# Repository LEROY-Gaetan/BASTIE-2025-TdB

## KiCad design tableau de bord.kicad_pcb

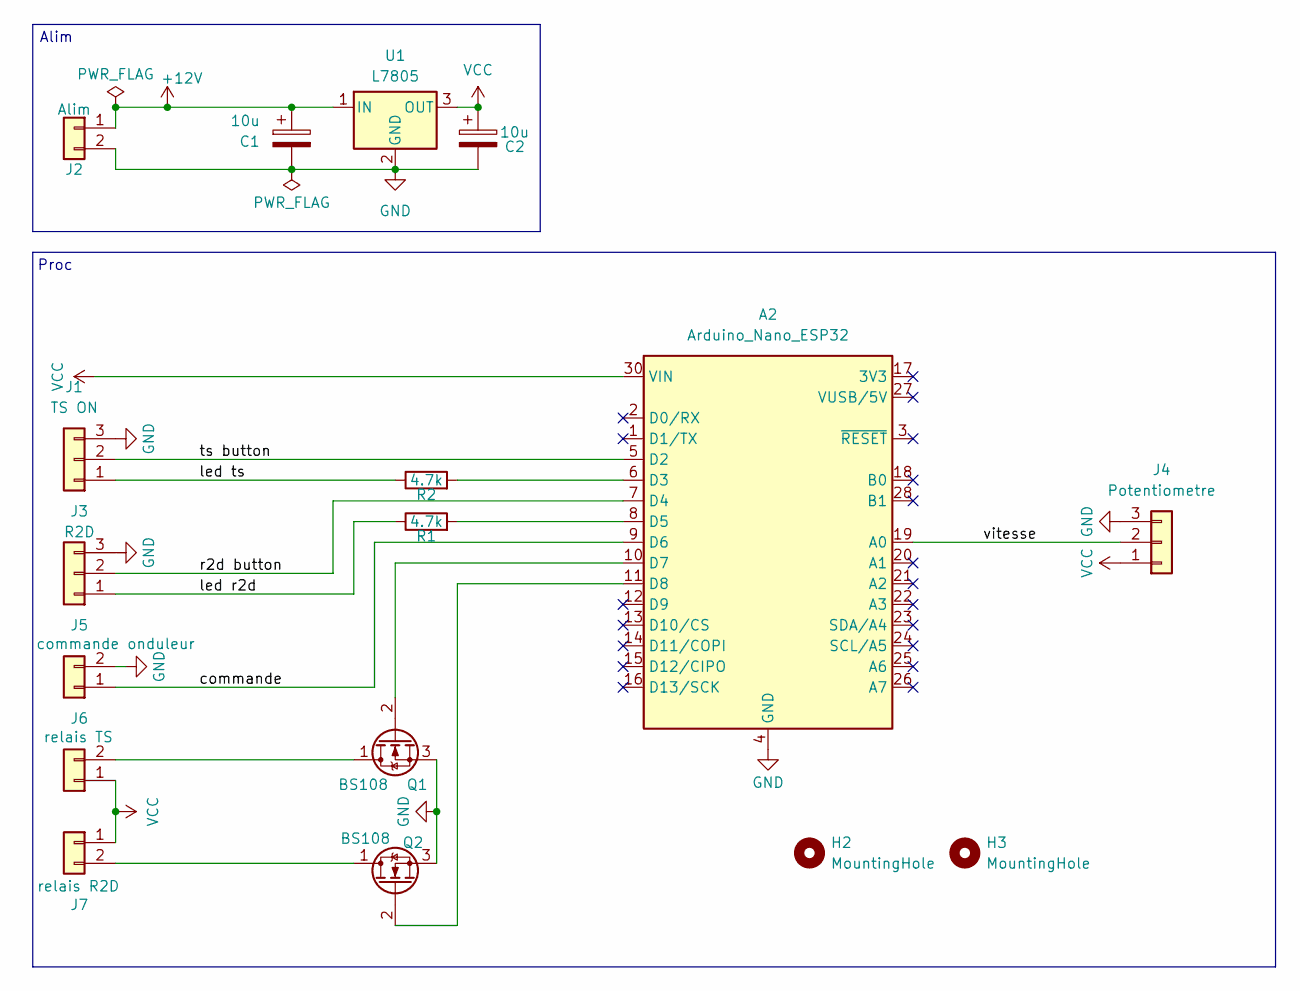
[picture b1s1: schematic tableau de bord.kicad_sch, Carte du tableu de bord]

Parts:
A2: Arduino_Nano_ESP32; Arduino_Nano
C1, C2: 10u; CP_Radial_D4.0mm_P1.50mm
H2, H3: MountingHole; MountingHole_2.2mm_M2
J1: TS ON; JST_XH_B3B-XH-A_1x03_P2.50mm_Vertical
J2: Alim; JST_XH_B2B-XH-A_1x02_P2.50mm_Vertical
J3: R2D; JST_XH_B3B-XH-A_1x03_P2.50mm_Vertical
J4: Potentiometre; JST_XH_B3B-XH-A_1x03_P2.50mm_Vertical
J5: commande onduleur; JST_XH_B2B-XH-A_1x02_P2.50mm_Vertical
J6: relais TS; JST_XH_B2B-XH-A_1x02_P2.50mm_Vertical
J7: relais R2D; JST_XH_B2B-XH-A_1x02_P2.50mm_Vertical
Q1, Q2: BS108; TO-92_Inline
R1, R2: 4.7k; R_Axial_DIN0204_L3.6mm_D1.6mm_P5.08mm_Horizontal
U1: L7805; TO-220-3_Horizontal_TabDown

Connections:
+12V: C1.1, J2.1, U1.1 (IN)
/commande: A2.9 (D6), J5.1
/led r2d: J3.1, R1.1
/led ts: J1.1, R2.1
/r2d button: A2.7 (D4), J3.2
/ts button: A2.5 (D2), J1.2
/vitesse: A2.19 (A0), J4.2
GND: A2.4 (GND), A2.29 (GND), C1.2, C2.2, J1.3, J2.2, J3.3, J4.3, J5.2, Q1.3 (S), Q2.3 (S), U1.2 (GND)
unnamed: A2.6 (D3), R2.2
unnamed: A2.8 (D5), R1.2
unnamed: A2.10 (D7), Q1.2 (G)
unnamed: A2.11 (D8), Q2.2 (G)
unnamed: J6.2, Q1.1 (D)
unnamed: J7.2, Q2.1 (D)
VCC: A2.30 (VIN), C2.1, J4.1, J6.1, J7.1, U1.3 (OUT)

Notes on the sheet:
Proc
Alim

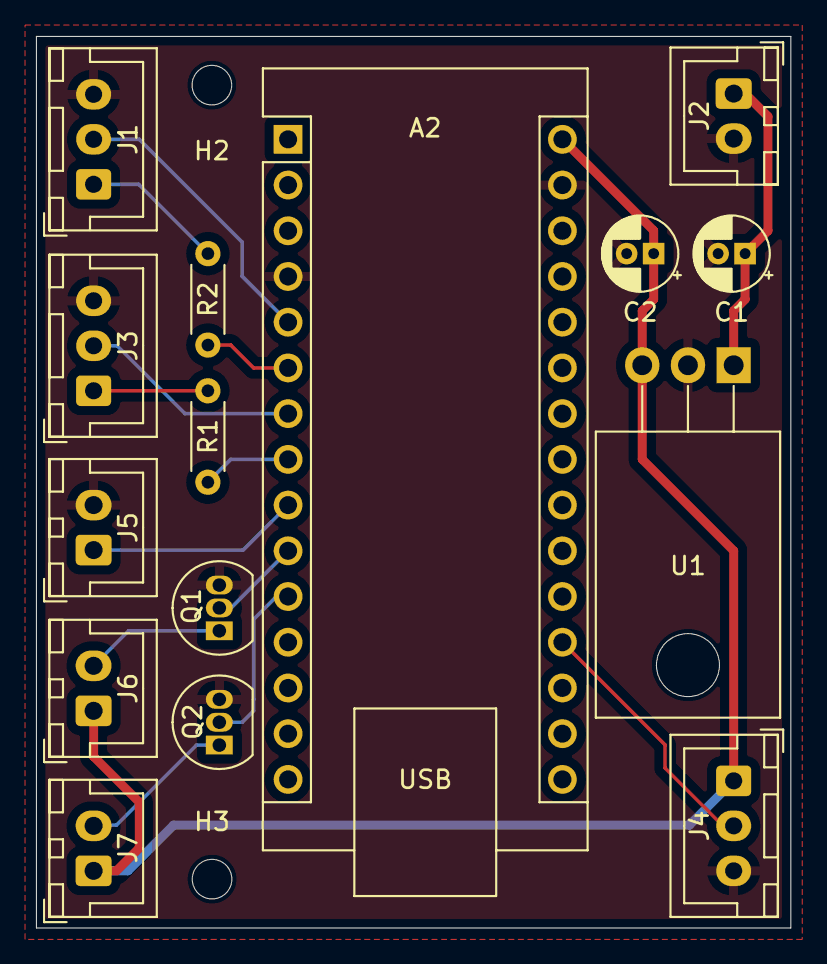
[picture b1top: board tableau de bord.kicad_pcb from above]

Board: 2 copper layers, 41.9 x 49.5 mm, 17 parts (0 on the bottom side), 15 nets.

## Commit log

2025-01-15 Import du projet KiCad
2025-01-15 Ajout des boutons I/O pour les scénario et pannes
2025-01-22 Retirer le voltmètre
2025-01-22 Revert "Retirer le voltmètre"
    This reverts commit f962c7fcb9cf469834c60d56faaa3777c9fbafc7.
2025-02-05 version prête pour révision
2025-02-05 Ajout de résistances pull down
2025-02-05 Ajout de résistances pull up
2025-03-19 Version 1
2025-03-19 Version 2:
    - ajout de mosfet pour commander les relais.
    - mise en forme des connecteurs
2025-04-09 Nouveaux connecteurs, amélioration de la qualité
2025-04-09 Revert "Nouveaux connecteurs, amélioration de la qualité"
    This reverts commit 7978c89d57e71e12e8c7bad613f2c47c352c5b43.
2025-04-16 Cleaning, retoring corrupted files
